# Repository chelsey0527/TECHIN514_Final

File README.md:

# Purrfect: Cat motion and humidity sensor
This system is designed to maintain an optimal environment for your cat, with a focus on keeping humidity and temperature at ideal levels. The default settings are 50% humidity and 26°C. However, when the cat is active, the system adjusts to 45% humidity and 24°C. Additionally, this device offers a pet location tracking feature.

## Sensor
This wearable module includes a battery, a humidity sensor, a motion sensor, and an MPU (Micro Processing Unit). Key components include:
- Seeduino XIAO ESP32S3
- Adafruit BME280: humidity and temperature sensor
- Adafruit MPU6050: motion sensor

## Display
The display unit features a battery, a processor, an OLED screen, a gauge, and a button, all integrated onto a custom PCB. This interface allows pet owners to monitor their cat's conditions and adjust the environment accordingly. It's a user-friendly system designed to keep your pet comfortable and healthy.
- stepper-motor-driven gauge: indicates the current humidity level
- LED: light when the device is on
- Button: to open device
- SSD1306 OLED: display readings

## Architecture

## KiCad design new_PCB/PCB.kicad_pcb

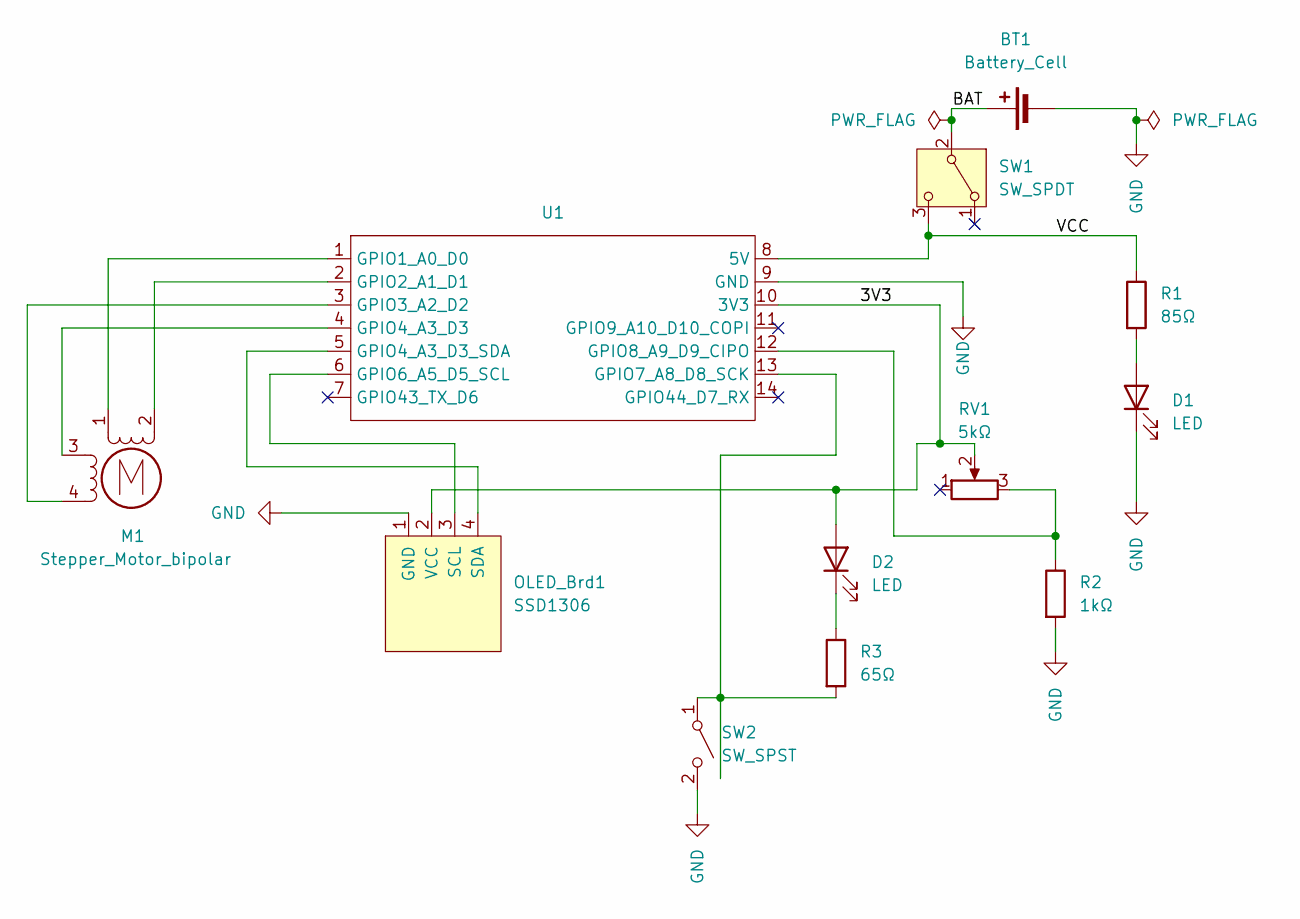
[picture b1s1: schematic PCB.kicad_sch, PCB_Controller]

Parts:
BT1: Battery_Cell; JST_NV_B02P-NV_1x02_P5.00mm_Vertical
D1, D2: LED; LED_0805_2012Metric_Pad1.15x1.40mm_HandSolder
M1: Stepper_Motor_bipolar; x27_stepper
OLED_Brd1: SSD1306; 128x64OLED
R1: 85Ω; R_0805_2012Metric_Pad1.20x1.40mm_HandSolder
R2: 1kΩ; R_0805_2012Metric_Pad1.20x1.40mm_HandSolder
R3: 65Ω; R_0805_2012Metric_Pad1.20x1.40mm_HandSolder
RV1: 5kΩ; Potentiometer_Piher_PC-16_Single_Horizontal
SW1: SW_SPDT; JST_EH_B3B-EH-A_1x03_P2.50mm_Vertical
SW2: SW_SPST; SW_PUSH-12mm
U1: XIAO_ESP32_SENSE

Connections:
/3V3: D2.2 (A), OLED_Brd1.2 (VCC), RV1.2, U1.10 (3V3)
/BAT: BT1.1 (+), SW1.2 (B)
/VCC: R1.1, SW1.3 (C), U1.8 (5V)
GND: BT1.2 (-), D1.1 (K), OLED_Brd1.1 (GND), R2.2, SW2.2 (B), U1.9 (GND)
unnamed: D1.2 (A), R1.2
unnamed: D2.1 (K), R3.1
unnamed: M1.2 (-), U1.2 (GPIO2_A1_D1)
unnamed: OLED_Brd1.3 (SCL), U1.6 (GPIO6_A5_D5_SCL)
unnamed: OLED_Brd1.4 (SDA), U1.5 (GPIO4_A3_D3_SDA)
unnamed: R3.2, SW2.1 (A), U1.13 (GPIO7_A8_D8_SCK)
unnamed: M1.1, U1.1 (GPIO1_A0_D0)
unnamed: M1.4, U1.3 (GPIO3_A2_D2)
unnamed: M1.3, U1.4 (GPIO4_A3_D3)
unnamed: R2.1, RV1.3, U1.12 (GPIO8_A9_D9_CIPO)

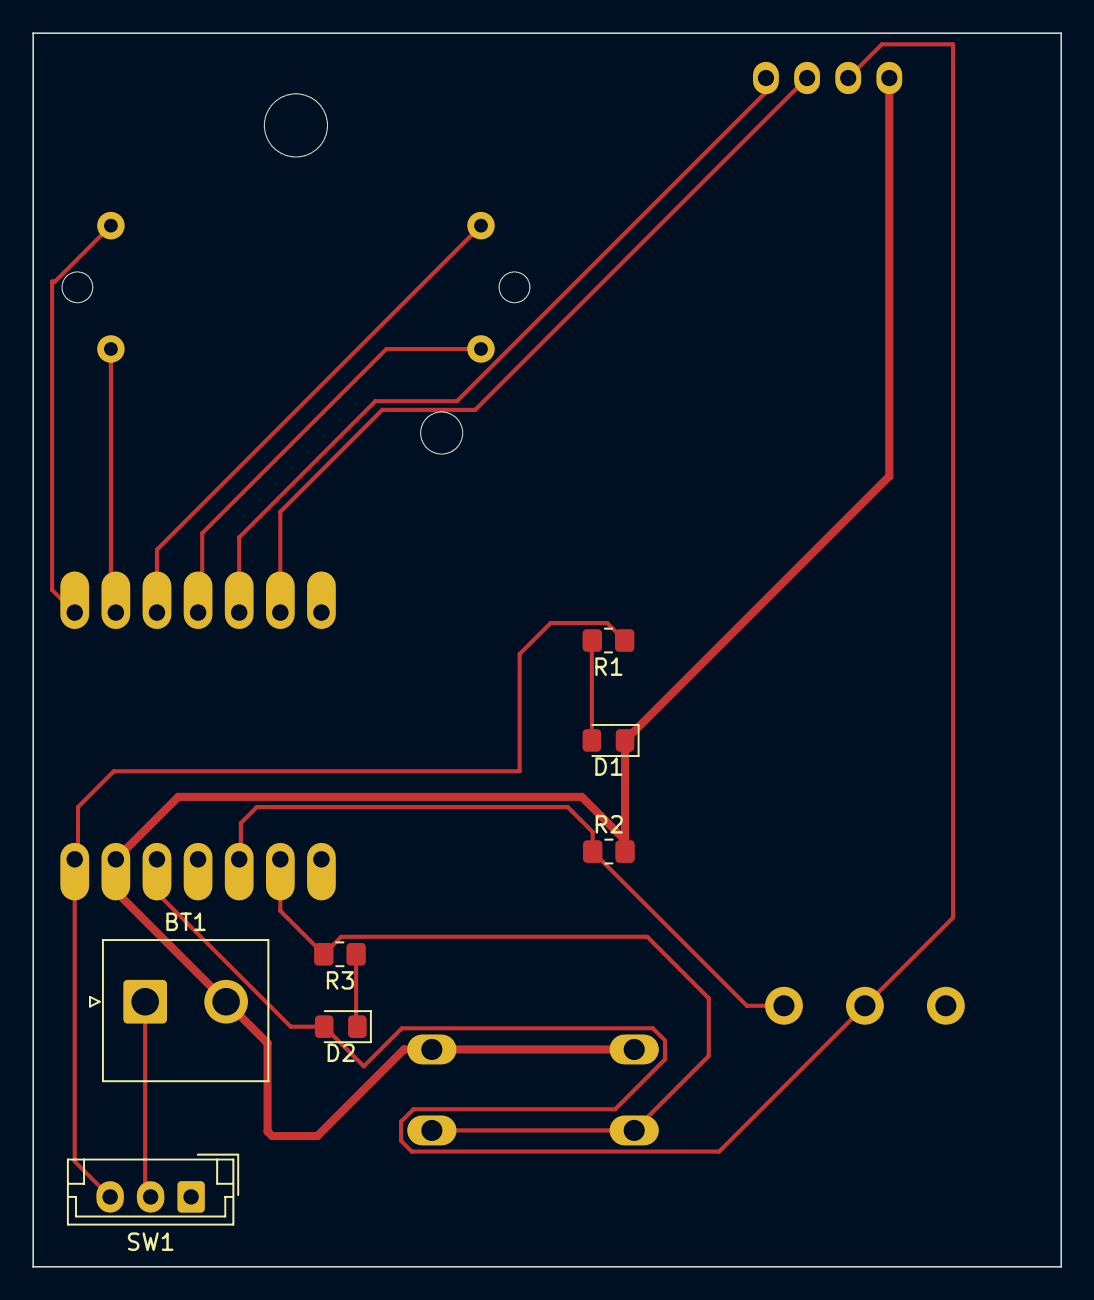
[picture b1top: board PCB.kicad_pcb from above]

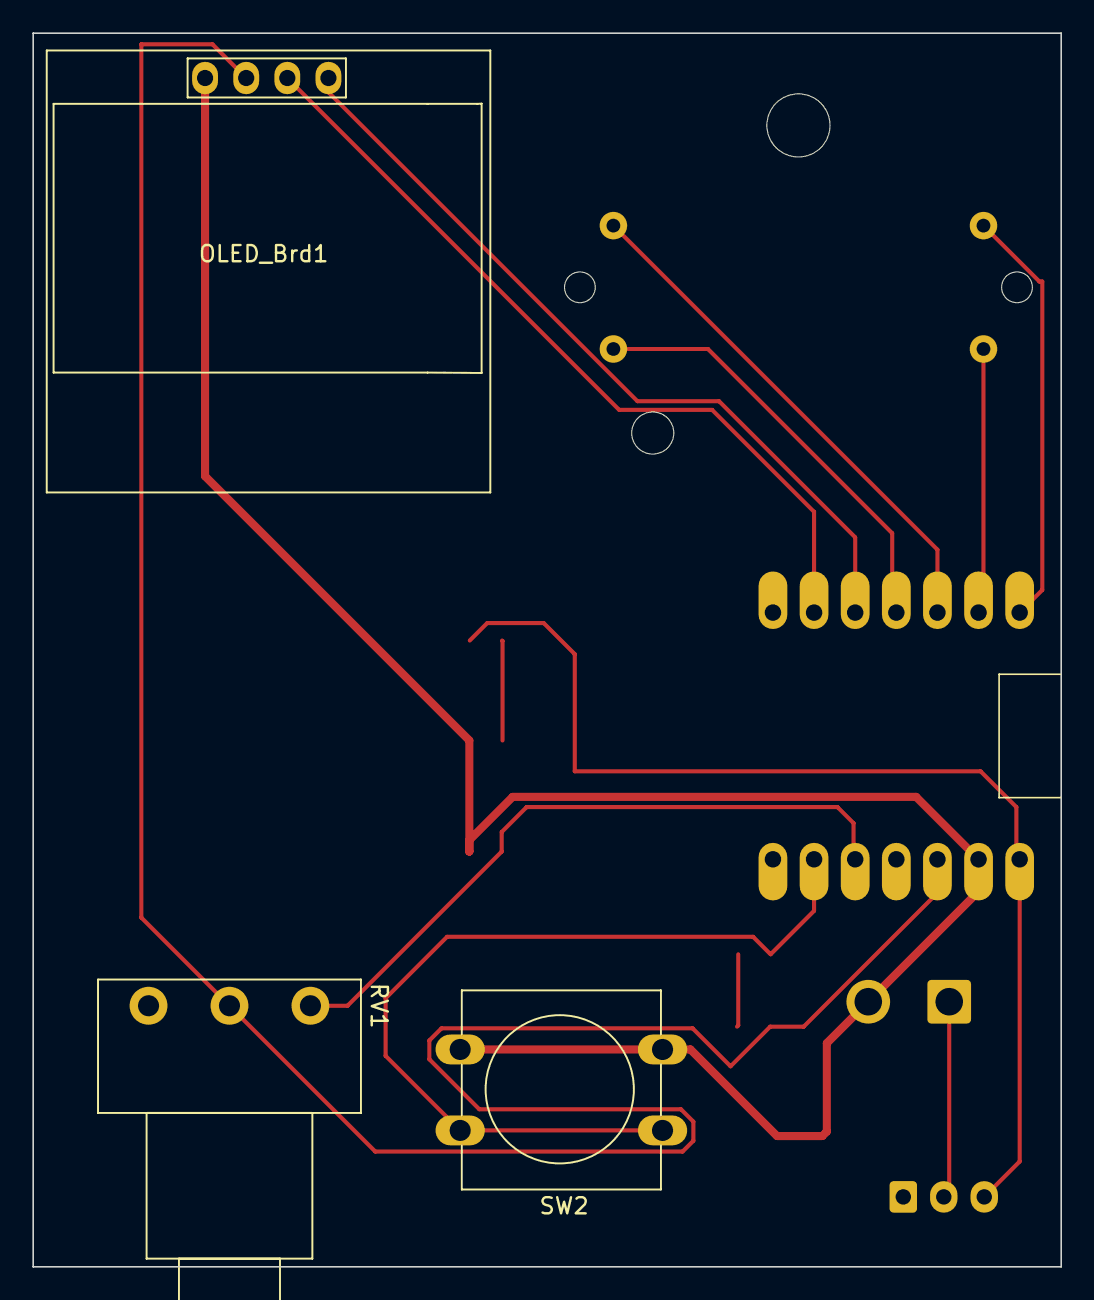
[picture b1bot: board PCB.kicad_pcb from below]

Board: 2 copper layers, 63.5 x 76.2 mm, 12 parts (5 on the bottom side), 14 nets.

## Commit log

2024-01-16 update datasheets
2024-01-17 updload README.md pdf
2024-01-18 ADD KiCAD files
2024-01-18 MODIFY README.md
2024-01-18 fix image
2024-01-18 update sketch
2024-01-18 update image
2024-01-18 change line
2024-01-21 fix typo
2024-01-21 fix path
2024-02-06 update datasheet
2024-02-06 more files
2024-02-07 update datsheet
2024-02-20 upload code
2024-02-29 update esp32 client code
2024-02-29 add server code
2024-02-29 add ml model
2024-02-29 merge
